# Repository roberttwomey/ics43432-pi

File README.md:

# ics43432-pi
ICS43432 mems mic for use with raspberry pi

Breakout board designed in EagleCAD. 

# ICS43432 Reference
http://www.invensense.com/wp-content/uploads/2015/02/ICS-43432_DS.pdf

# Kernel Module Installation

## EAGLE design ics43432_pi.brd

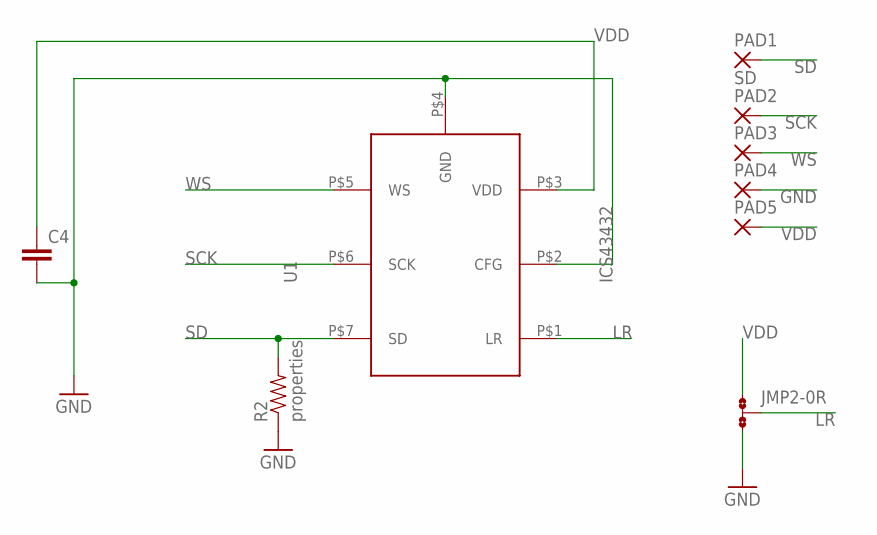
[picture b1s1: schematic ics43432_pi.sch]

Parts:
C4: CAP0402-CAP; 0402-CAP
JMP2: 0R-JUMPC; C0R-JMP
PAD1: SD; SMD1,27-2,54
PAD2, PAD3, PAD4, PAD5: SMD2; SMD1,27-2,54
R2: properties; 0402-RES
U1: ICS43432

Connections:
GND: C4.2, JMP2.3, PAD4.1, R2.1, U1.P$2 (CFG), U1.P$4 (GND)
LR: JMP2.2, U1.P$1 (LR)
SCK: PAD2.1, U1.P$6 (SCK)
SD: PAD1.1, R2.2, U1.P$7 (SD)
VDD: C4.1, JMP2.1, PAD5.1, U1.P$3 (VDD)
WS: PAD3.1, U1.P$5 (WS)

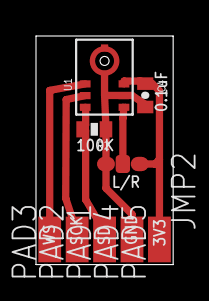
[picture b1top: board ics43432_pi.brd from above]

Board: 2 copper layers, 7.6 x 12.7 mm, 9 parts (0 on the bottom side), 6 nets.

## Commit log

2017-01-02 renamed files
2017-01-07 added photos of assembled circuits

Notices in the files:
parts and their libraries:
SparkFun-Capacitors: Licensing: Creative Commons ShareAlike 4.0 International - https://creativecommons.org/licenses/by-sa/4.0
